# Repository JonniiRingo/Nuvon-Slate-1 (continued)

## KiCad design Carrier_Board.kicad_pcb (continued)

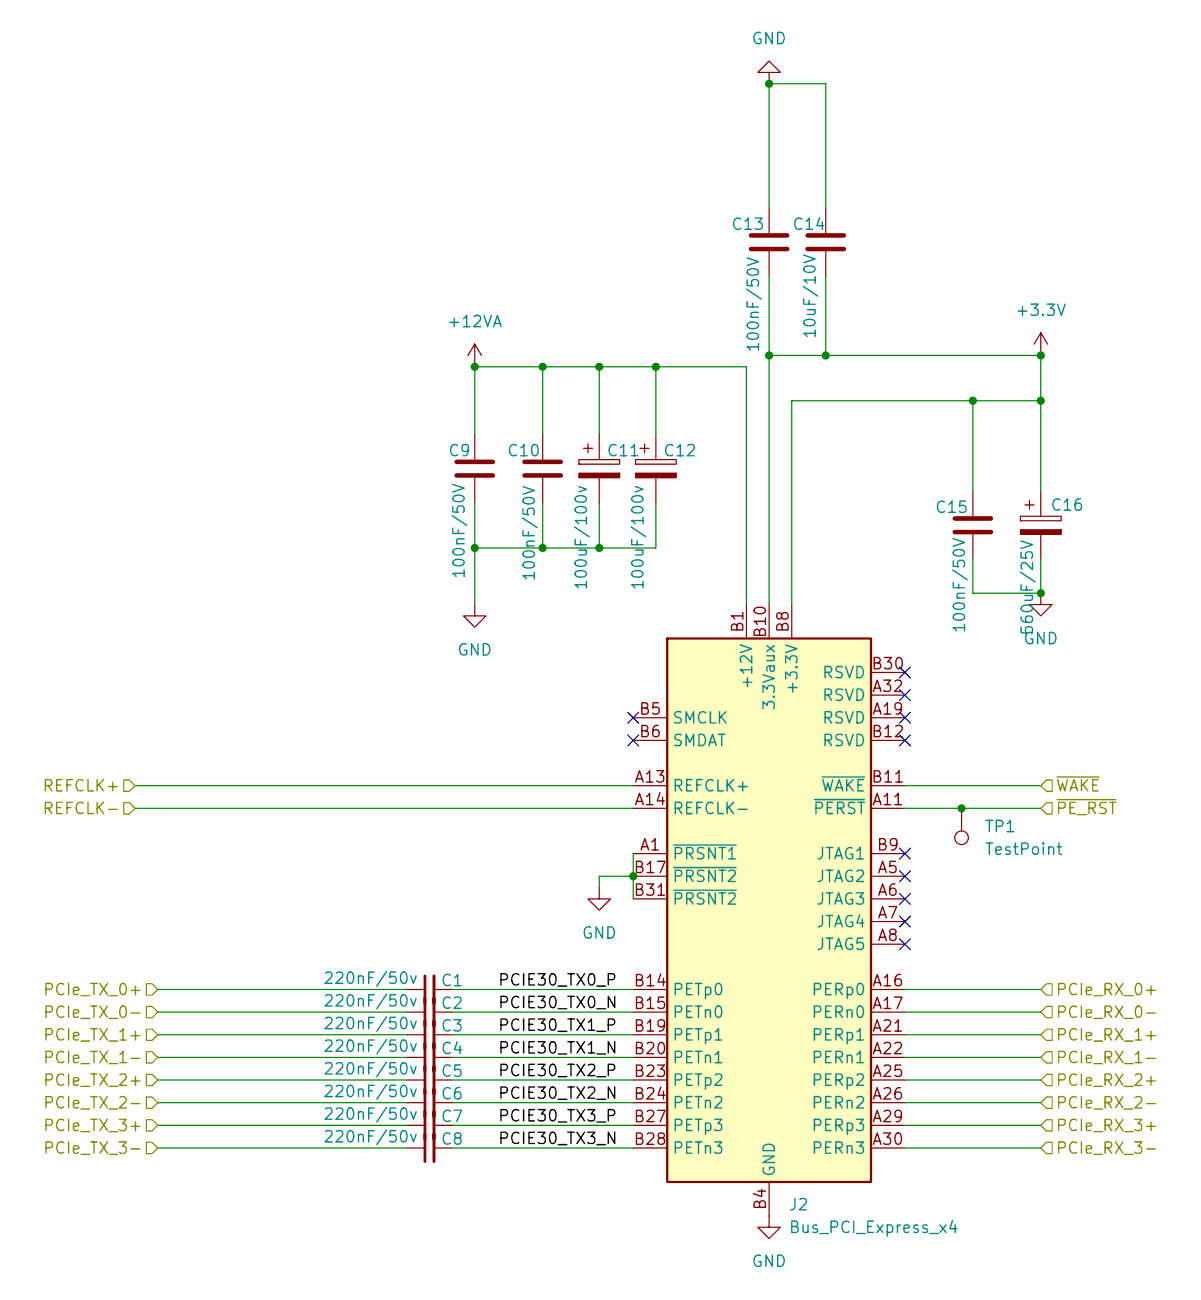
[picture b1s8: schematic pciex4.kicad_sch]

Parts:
C1, C2, C3, C4, C5, C6, C7, C8: 220nF/50v; C_0402_1005Metric
C9, C10, C13, C15: 100nF/50V; C_0402_1005Metric
C11, C12: 100uF/100v; CP_Elec_6.3x7.7
C14: 10uF/10V; C_0402_1005Metric
C16: 560uF/25V; CP_Elec_6.3x7.7
J2: Bus_PCI_Express_x4; PCIe_x4_Gen3Slot_Connectors
TP1: TestPoint; TestPoint_Pad_D1.5mm

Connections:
+3.3V: C13.2, C14.2, C15.1, C16.1, J2.A9 (+3.3V), J2.A10 (+3.3V), J2.B8 (+3.3V), J2.B10 (3.3Vaux); also elsewhere on the board
+12VA: C9.1, C10.1, C11.1, C12.1, J2.A2 (+12V), J2.A3 (+12V), J2.B1 (+12V), J2.B2 (+12V), J2.B3 (+12V); also elsewhere on the board
/LattePanda Module/HSIO_8_RX+: J2.A16 (PERp0); also elsewhere on the board
/LattePanda Module/HSIO_8_RX-: J2.A17 (PERn0); also elsewhere on the board
/LattePanda Module/HSIO_8_TX+: C1.1; also elsewhere on the board
/LattePanda Module/HSIO_8_TX-: C2.1; also elsewhere on the board
/LattePanda Module/HSIO_9_RX+: J2.A21 (PERp1); also elsewhere on the board
/LattePanda Module/HSIO_9_RX-: J2.A22 (PERn1); also elsewhere on the board
/LattePanda Module/HSIO_9_TX+: C3.1; also elsewhere on the board
/LattePanda Module/HSIO_9_TX-: C4.1; also elsewhere on the board
/LattePanda Module/HSIO_10_RX+: J2.A25 (PERp2); also elsewhere on the board
/LattePanda Module/HSIO_10_RX-: J2.A26 (PERn2); also elsewhere on the board
/LattePanda Module/HSIO_10_TX+: C5.1; also elsewhere on the board
/LattePanda Module/HSIO_10_TX-: C6.1; also elsewhere on the board
/LattePanda Module/HSIO_11_RX+: J2.A29 (PERp3); also elsewhere on the board
/LattePanda Module/HSIO_11_RX-: J2.A30 (PERn3); also elsewhere on the board
/LattePanda Module/HSIO_11_TX+: C7.1; also elsewhere on the board
/LattePanda Module/HSIO_11_TX-: C8.1; also elsewhere on the board
/LattePanda Module/REFCLK2+: J2.A13 (REFCLK+); also elsewhere on the board
/LattePanda Module/REFCLK2-: J2.A14 (REFCLK-); also elsewhere on the board
/PCIe x4/PCIE30_TX0_N: C2.2, J2.B15 (PETn0)
/PCIe x4/PCIE30_TX0_P: C1.2, J2.B14 (PETp0)
/PCIe x4/PCIE30_TX1_N: C4.2, J2.B20 (PETn1)
/PCIe x4/PCIE30_TX1_P: C3.2, J2.B19 (PETp1)
/PCIe x4/PCIE30_TX2_N: C6.2, J2.B24 (PETn2)
/PCIe x4/PCIE30_TX2_P: C5.2, J2.B23 (PETp2)
/PCIe x4/PCIE30_TX3_N: C8.2, J2.B28 (PETn3)
/PCIe x4/PCIE30_TX3_P: C7.2, J2.B27 (PETp3)
/~PLT_RST: J2.A11 (~PERST), TP1.1 (1_1); also elsewhere on the board
/~WAKE: J2.B11 (~WAKE); also elsewhere on the board
GND: C9.2, C10.2, C11.2, C12.2, C13.1, C14.1, C15.2, C16.2, J2.A1 (~PRSNT1), J2.A4 (GND), J2.A12 (GND), J2.A15 (GND), J2.A18 (GND), J2.A20 (GND), J2.A23 (GND), J2.A24 (GND), J2.A27 (GND), J2.A28 (GND), J2.A31 (GND), J2.B4 (GND), J2.B7 (GND), J2.B13 (GND), J2.B16 (GND), J2.B17 (~PRSNT2), J2.B18 (GND), J2.B21 (GND), J2.B22 (GND), J2.B25 (GND), J2.B26 (GND), J2.B29 (GND), J2.B31 (~PRSNT2), J2.B32 (GND); also elsewhere on the board

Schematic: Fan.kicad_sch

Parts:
C84, C85: 100nF/50V; C_0402_1005Metric
D26, D27: 1N5819WS; D_SOD-323
JP2: SolderJumper_2_Open; SolderJumper-2_P1.3mm_Bridged_RoundedPad1.0x1.5mm
M1, M2: Fan_4pin; JST_PH_B4B-PH-K_1x04_P2.00mm_Vertical
R63: 10k/1%; R_0402_1005Metric
R64, R65, R72, R74, R75: 4.7k/1%; R_0402_1005Metric
R67, R68, R70, R206: 21.5k/1%; R_0402_1005Metric
R69, R71: 100/1%; R_0402_1005Metric
R73: 0/1%; R_0201_0603Metric
TH1: Thermistor_NTC; R_0603_1608Metric
TP12, TP88: TestPoint; TestPoint_Pad_D1.5mm

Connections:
+3.3V: R63.2, R64.2, R65.2; also elsewhere on the board
+5V: C84.1, D26.1 (K), M1.2 (+), R72.1, R73.1; also elsewhere on the board
+12V: R75.1; also elsewhere on the board
/Fan/FAN_1_PWM: R69.1, TP12.1 (1_1); also elsewhere on the board
/Fan/FAN_1_TAC: R64.1, R68.1, R206.2, TP88.1 (1_1); also elsewhere on the board
/Fan/FAN_2_PWM: R71.1; also elsewhere on the board
/Fan/FAN_2_TAC: R65.1, R67.2, R70.1; also elsewhere on the board
/Fan/TEMP: JP2.1 (A); also elsewhere on the board
GND: C84.2, C85.2, M1.1 (-), M2.1 (-), R67.1, R206.1, TH1.2; also elsewhere on the board
unnamed: D26.2 (A), M1.3 (Tacho), R68.2, R72.2
unnamed: D27.2 (A), M2.3 (Tacho), R70.2, R74.2
unnamed: C85.1, D27.1 (K), M2.2 (+), R73.2, R74.1, R75.2
unnamed: JP2.2 (B), R63.1, TH1.1
unnamed: M1.4 (PWM), R69.2
unnamed: M2.4 (PWM), R71.2

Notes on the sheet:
Reserved for 12V fan FAN_TAC input ony allows 3.3v level
SYS FAN
LattePanda Mu has integrated pull-up resistors (which we will not be using J.S. 2026)
CPU FAN

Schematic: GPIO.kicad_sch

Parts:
J7, J9, J12, J13, J19, J20, J21: Conn_01x04_Pin; PinHeader_1x04_P2.54mm_Vertical
J8, J10, J11, J14: Conn_01x03_Pin; PinHeader_1x03_P2.54mm_Vertical
U9, U10, U11, U12: D3V3XA4B10LP; Diodes_UDFN-10_1.0x2.5mm_P0.5mm
U17: D3V3XA4B10LP; Diodes_UDFN-10_1x2.5mm_P0.5mm

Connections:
+3.3V: J13.1, J13.2, J13.3, J13.4, J14.1, J14.2, J14.3, J21.1, J21.2, J21.3, J21.4; also elsewhere on the board
/GPIO/GPP_D0: J19.1, U17.1, U17.10 (NC); also elsewhere on the board
/GPIO/GPP_D1: J19.2, U17.2, U17.9 (NC); also elsewhere on the board
/GPIO/GPP_D2: J19.3, U17.4, U17.7 (NC); also elsewhere on the board
/GPIO/GPP_D3: J19.4, U17.5, U17.6 (NC); also elsewhere on the board
/GPIO/I2C2_SCL: J9.1, U11.1, U11.10 (NC); also elsewhere on the board
/GPIO/I2C2_SDA: J7.1, U9.1, U9.10 (NC); also elsewhere on the board
/GPIO/I2C3_SCL: J9.2, U11.2, U11.9 (NC); also elsewhere on the board
/GPIO/I2C3_SDA: J7.2, U9.2, U9.9 (NC); also elsewhere on the board
/GPIO/I2C4_SCL: J9.3, U11.4, U11.7 (NC); also elsewhere on the board
/GPIO/I2C4_SDA: J7.3, U9.4, U9.7 (NC); also elsewhere on the board
/GPIO/I2C5_SCL: J9.4, U11.5, U11.6 (NC); also elsewhere on the board
/GPIO/I2C5_SDA: J7.4, U9.5, U9.6 (NC); also elsewhere on the board
/GPIO/SOC_UART0_RX: J8.1, U10.1, U10.10 (NC); also elsewhere on the board
/GPIO/SOC_UART0_TX: J10.1, U12.1, U12.10 (NC); also elsewhere on the board
/GPIO/SOC_UART1_RX: J8.2, U10.2, U10.9 (NC); also elsewhere on the board
/GPIO/SOC_UART1_TX: J10.2, U12.2, U12.9 (NC); also elsewhere on the board
/GPIO/SOC_UART2_RX: J8.3, U10.4, U10.7 (NC); also elsewhere on the board
/GPIO/SOC_UART2_TX: J10.3, U12.4, U12.7 (NC); also elsewhere on the board
GND: J11.1, J11.2, J11.3, J12.1, J12.2, J12.3, J12.4, J20.1, J20.2, J20.3, J20.4, U9.3 (VSS), U9.8 (VSS), U10.3 (VSS), U10.8 (VSS), U11.3 (VSS), U11.8 (VSS), U12.3 (VSS), U12.8 (VSS), U17.3 (VSS), U17.8 (VSS); also elsewhere on the board
unnamed: U10.5, U10.6 (NC)
unnamed: U12.5, U12.6 (NC)

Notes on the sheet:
I2C have internal 2.2k resistor pull-up to 3V3 on som board
I2C
UART

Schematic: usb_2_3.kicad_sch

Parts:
C26, C27, C28, C29: 100NF/50V; C_0402_1005Metric
C30, C31, C32: 22mF/10V; C_0603_1608Metric
D5, D6, D7, D8: ESD9B5.0ST5G; D_0402_1005Metric
F2, F3, F4, F5: 6V/1A; Fuse_0805_2012Metric
J4: USB3_A_Stacked; USB3_A_Molex_48406-0001_Horizontal_Stacked
J5: USB_A_Stacked; USB_A_CUI_UJ2-ADH-TH_Horizontal_Stacked
U3, U4, U5: D3V3XA4B10LP; Diodes_UDFN-10_1.0x2.5mm_P0.5mm

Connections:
+5V: C30.2, C31.2, C32.2, F2.1, F3.1, F4.1, F5.1; also elsewhere on the board
/LattePanda Module/HSIO_0_TX+: C27.1; also elsewhere on the board
/LattePanda Module/HSIO_0_TX-: C26.1; also elsewhere on the board
/LattePanda Module/HSIO_1_TX+: C29.1; also elsewhere on the board
/LattePanda Module/HSIO_1_TX-: C28.1; also elsewhere on the board
/USB 2.0 & 3.0/CON_USB1_D_N: J5.2 (D1-), U4.4, U4.7 (NC); also elsewhere on the board
/USB 2.0 & 3.0/CON_USB1_D_P: J5.3 (D1+), U4.5, U4.6 (NC); also elsewhere on the board
/USB 2.0 & 3.0/CON_USB2_D_N: J5.6 (D2-), U4.1, U4.10 (NC); also elsewhere on the board
/USB 2.0 & 3.0/CON_USB2_D_P: J5.7 (D2+), U4.2, U4.9 (NC); also elsewhere on the board
/USB 2.0 & 3.0/CON_USB3_D_N: D8.1 (A1), J4.2 (D1-); also elsewhere on the board
/USB 2.0 & 3.0/CON_USB3_D_P: D7.1 (A1), J4.3 (D1+); also elsewhere on the board
/USB 2.0 & 3.0/CON_USB3_SSRX_N: J4.5 (SSRX1-); also elsewhere on the board
/USB 2.0 & 3.0/CON_USB3_SSRX_P: J4.6 (SSRX1+), U5.4, U5.7 (NC); also elsewhere on the board
/USB 2.0 & 3.0/CON_USB3_SSTX_N: C26.2, J4.8 (SSTX1-), U3.4, U3.7 (NC)
/USB 2.0 & 3.0/CON_USB3_SSTX_P: C27.2, J4.9 (SSTX1+), U3.5, U3.6 (NC)
/USB 2.0 & 3.0/CON_USB4_D_N: D6.1 (A1), J4.11 (D2-); also elsewhere on the board
/USB 2.0 & 3.0/CON_USB4_D_P: D5.1 (A1), J4.12 (D2+); also elsewhere on the board
/USB 2.0 & 3.0/CON_USB4_SSRX_N: J4.14 (SSRX2-), U5.2, U5.9 (NC); also elsewhere on the board
/USB 2.0 & 3.0/CON_USB4_SSRX_P: J4.15 (SSRX2+), U5.1, U5.10 (NC); also elsewhere on the board
/USB 2.0 & 3.0/CON_USB4_SSTX_N: C28.2, J4.17 (SSTX2-), U3.1, U3.10 (NC)
/USB 2.0 & 3.0/CON_USB4_SSTX_P: C29.2, J4.18 (SSTX2+), U3.2, U3.9 (NC)
GND: C30.1, C31.1, C32.1, D5.2 (A2), D6.2 (A2), D7.2 (A2), D8.2 (A2), J4.4 (GND1), J4.7 (DRAIN1), J4.13 (GND2), J4.16 (DRAIN2), J4.SH (SHIELD), J5.4 (GND1), J5.8 (GND2), J5.SH (Shield), U3.3 (VSS), U3.8 (VSS), U4.3 (VSS), U4.8 (VSS), U5.3 (VSS), U5.8 (VSS); also elsewhere on the board
unnamed: F4.2, J4.1 (VBUS1)
unnamed: F5.2, J4.10 (VBUS2)
unnamed: F2.2, J5.1 (VBUS1)
unnamed: F3.2, J5.5 (VBUS2)
unnamed: U5.5, U5.6 (NC)

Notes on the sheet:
ESD protection for the USB 3.0 data lines
USB 2.0
USB 3.0

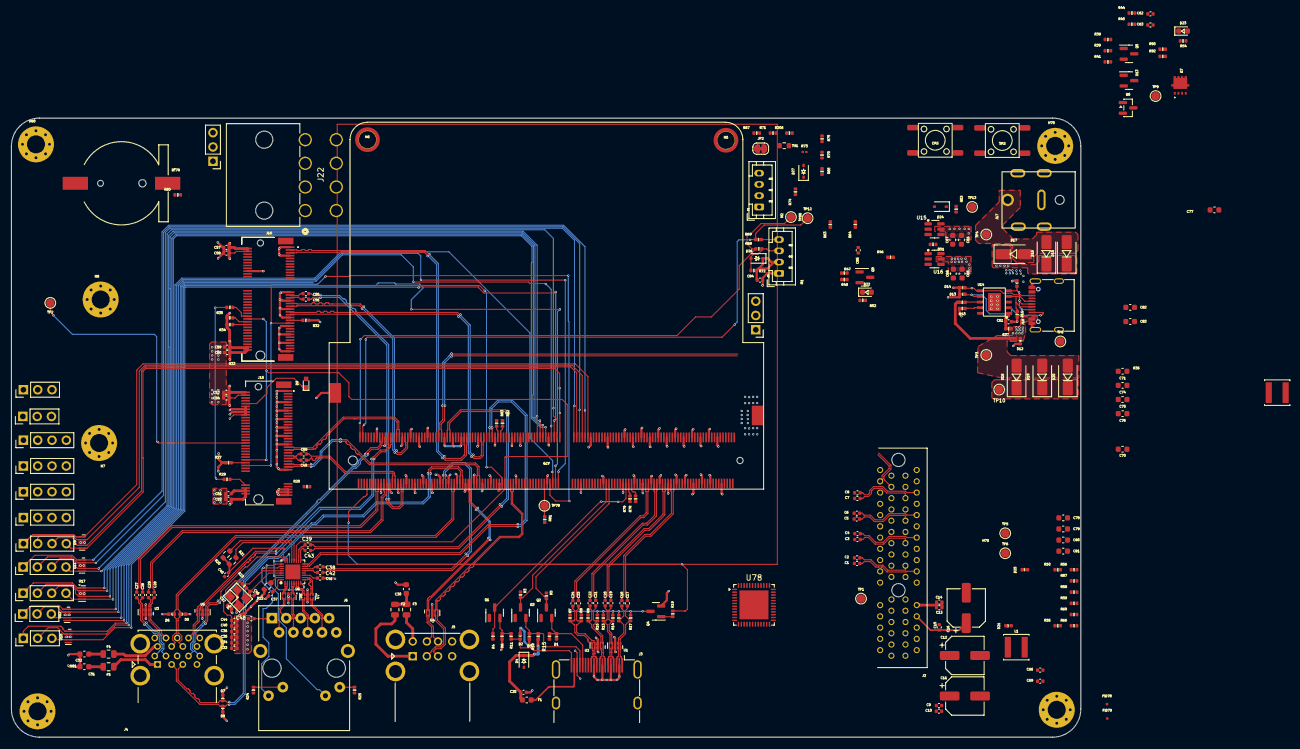
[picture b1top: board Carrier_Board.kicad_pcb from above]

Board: 4 copper layers, 190.0 x 110.0 mm, 271 parts (0 on the bottom side), 215 nets.

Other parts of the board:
J15: Bus_M.2_Socket_M; PCIe_M.2_Connectors_P=0.5mm_H=4.2mm_KeyM
J16: Bus_M.2_Socket_E; PCIe_M.2_Connectors_P=0.5mm_H=4.2mm_KeyE

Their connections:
+3.3V: J15.2 (3.3V), J15.4 (3.3V), J15.12 (3.3V), J15.14 (3.3V), J15.16 (3.3V), J15.18 (3.3V), J15.70 (3.3V), J15.72 (3.3V), J15.74 (3.3V), J16.2 (3.3V), J16.4 (3.3V), J16.72 (3.3V), J16.74 (3.3V); also elsewhere on the board
/LattePanda Module/HSIO_2_RX+: J15.43 (PERp0/SATA-B-); also elsewhere on the board
/LattePanda Module/HSIO_2_RX-: J15.41 (PERn0/SATA-B+); also elsewhere on the board
/LattePanda Module/HSIO_3_RX+: J16.41 (PERp0); also elsewhere on the board
/LattePanda Module/HSIO_3_RX-: J16.43 (PERn0); also elsewhere on the board
/LattePanda Module/REFCLK0+: J15.55 (REFCLKp); also elsewhere on the board
/LattePanda Module/REFCLK0-: J15.53 (REFCLKn); also elsewhere on the board
/LattePanda Module/REFCLK3+: J16.47 (REFCLKp0); also elsewhere on the board
/LattePanda Module/REFCLK3-: J16.49 (REFCLKn0); also elsewhere on the board
/LattePanda Module/USB_2_P7+: J16.3 (USB_D+); also elsewhere on the board
/LattePanda Module/USB_2_P7-: J16.5 (USB_D-); also elsewhere on the board
/M.2 M Key/CLKREQE: J16.53 (~CLKREQ0); also elsewhere on the board
/M.2 M Key/CLKREQM: J15.52 (~CLKREQ); also elsewhere on the board
/M.2 M Key/CON_PCIE_TX0+: J16.35 (PETp0); also elsewhere on the board
/M.2 M Key/CON_PCIE_TX0-: J16.37 (PETn0); also elsewhere on the board
/M.2 M Key/CON_PCIE_TX1+: J15.49 (PETp0/SATA-A+); also elsewhere on the board
/M.2 M Key/CON_PCIE_TX1-: J15.47 (PETn0/SATA-A-); also elsewhere on the board
/~PLT_RST: J15.50 (~PERST), J16.52 (~PERST0); also elsewhere on the board
/~WAKE: J15.54 (~PEWAKE), J16.55 (~PEWAKE0); also elsewhere on the board
GND: J15.1 (GND), J15.3 (GND), J15.9 (GND), J15.15 (GND), J15.21 (GND), J15.27 (GND), J15.33 (GND), J15.39 (GND), J15.45 (GND), J15.51 (GND), J15.57 (GND), J15.71 (GND), J15.73 (GND), J15.75 (GND), J16.1 (GND), J16.7 (GND), J16.18 (GND), J16.33 (GND), J16.39 (GND), J16.45 (GND), J16.51 (GND), J16.57 (GND), J16.63 (GND), J16.69 (GND), J16.75 (GND); also elsewhere on the board
unnamed 158: J15.10 (DAS/~DSS/~LED1); also elsewhere on the board
unnamed 175: J15.38 (DEVSLP); also elsewhere on the board
unnamed 176: J15.69 (PEDET); also elsewhere on the board
unnamed 177: J15.68 (SUSCLK); also elsewhere on the board
unnamed 178: J16.50 (SUSCLK); also elsewhere on the board
unnamed 179: J16.56 (~W_DISABLE1); also elsewhere on the board
unnamed 180: J16.54 (~W_DISABLE2); also elsewhere on the board

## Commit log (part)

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2026-05-26 Schematic setup complete. Symbols and footprints imported from official design files.
2026-05-28 Imported official netclasses and selected thec correct grid settings to avoid future mistakes
2026-05-28 Created heirachical sheets
2026-05-28 Added mounting holes and Fiducials
2026-05-28 Started with the LattePanda module. Unconnected and some other various initial configs
2026-05-28 Fixed an unconnected pin on the lattepanda module sub schema
2026-05-28 Added module pin symnbols and pull down resistors
2026-05-28 Hierichal labels added for the modul sheet
2026-05-29 Added hierachical labels to the main scheematic
2026-05-29 Canged the position of the pins in the main sheet
2026-05-31 Rearranged the hiearchal labels in module and main sheets
2026-06-02 Started the power circuit schematic sheet
2026-06-02 wired up the power management ic to the usbc j connector
2026-06-02 Added the circuit for the barrel jack in the PSU schematic sheet
2026-06-02 Populated the PCU with passive parts inline before wiring up the schematic and finding correct IC's to intefrate into the system
2026-06-02 Implimented the sub circuit for the PCIe x4 lanes Power for PCIe x4 0VP@13.86V
2026-06-02 Added the 3.3v and the 5V power regulator sub circuits in the PSU schematic sheet
2026-06-03 Added the power and the restet button sub circuits to the psu shematic sheet
2026-06-03 staging for the grid fix
2026-06-03 Fixed the grid settings and now need to fix all the unconnected wires
2026-06-04 chore: ignore KiCad backups and lock files
2026-06-04 Fixed the Grid connection errors in the PSU Schematic sheet
2026-06-05 Wired the hierichal sheets together for the PSU and the main MU Module
2026-06-05 Added the ESSOP official footprint for the IC in the PSU sheet that was missing
2026-06-06 Sheet complete for the fan
2026-06-06 Connected the hierarchal sheets together for the fan and the Mu moduls on the main sheet level and also added the label for the extrnal temp sensor for thermistor
2026-06-06 Adde the label and the connection for the thermisistor and populated the unconnected sub circuits for the fans and the system fans
2026-06-07 Adde the sub sheet schematic for the GPIO and connected the Hierchal sheets together
2026-06-09 finished the pciex4 implememntation
2026-06-09 Connected the hierchal labels to the main mu module in the root sheet
2026-06-09 Finished part of the M.2. schematic capture
2026-06-09 Finished the shematic capture of the M.2 sheet but still have to assign the footprints
2026-06-09 Finishing up the schematic for the gigabit ethernet
2026-06-09 Connected the hierarchical labels in the root sheet to the gigabit ethernet
2026-06-10 Fixed some ERC errors int the gigabit sub schema
2026-06-10 Untrack and ignore .history
2026-06-10 Verification commit
2026-06-10 Finished the schematic capture for the USb 2.0/3.0
2026-06-10 Fixed the labels to the netlabels in the USB schema sheet
2026-06-11 Connected the usb sheets together in the the roor sheet
2026-06-11 Fixed the erc power fleag erro in the USB sub sheet
2026-06-11 Finished the schematic capture for thel HDMI
2026-06-11 Finished the HDMI circuit and connected labels to Mu model in root sheet
2026-06-13 finished the entire schematic capture for each of the sub sheets .and then the next part is to .fix all the erc errors when impoting the shematic in to the pcb to get readu for routing
2026-06-14 Fixed annotation errors duplicate designators on passive components R11 and J15 so that schematic could be imported into pcb. There might be some missing footprints... starting that investigation
2026-06-17 Annotation complete and schematic imported to pcb. Footprint investigatoin in-process.
2026-06-17 Updated all the footprints into the pcb editor but all the designator numbers have changed... I have tp go back and fix each one
2026-06-23 Designators in PSU restored
2026-06-23 Designators in ethernet restored
2026-06-23 Designators in HDMI restored
2026-06-23 Designators in pcie restored
2026-06-23 Designators in GPIO restored
2026-06-23 USB designators restored
2026-06-23 Designators in fans restored
2026-06-23 Designators in M.2 restored
2026-06-26 added the impedance stackup calculation parameters for high speed traces in routing phase
